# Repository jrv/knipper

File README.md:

# knipper
Simple 555 blinking leds schematic for car direction lights

This is a KiCad desing for the blinking lights of our Spijkstaal electric vehicle. It also switches the reverse lights via a MosFet, with a 5V signal from the motor controller.

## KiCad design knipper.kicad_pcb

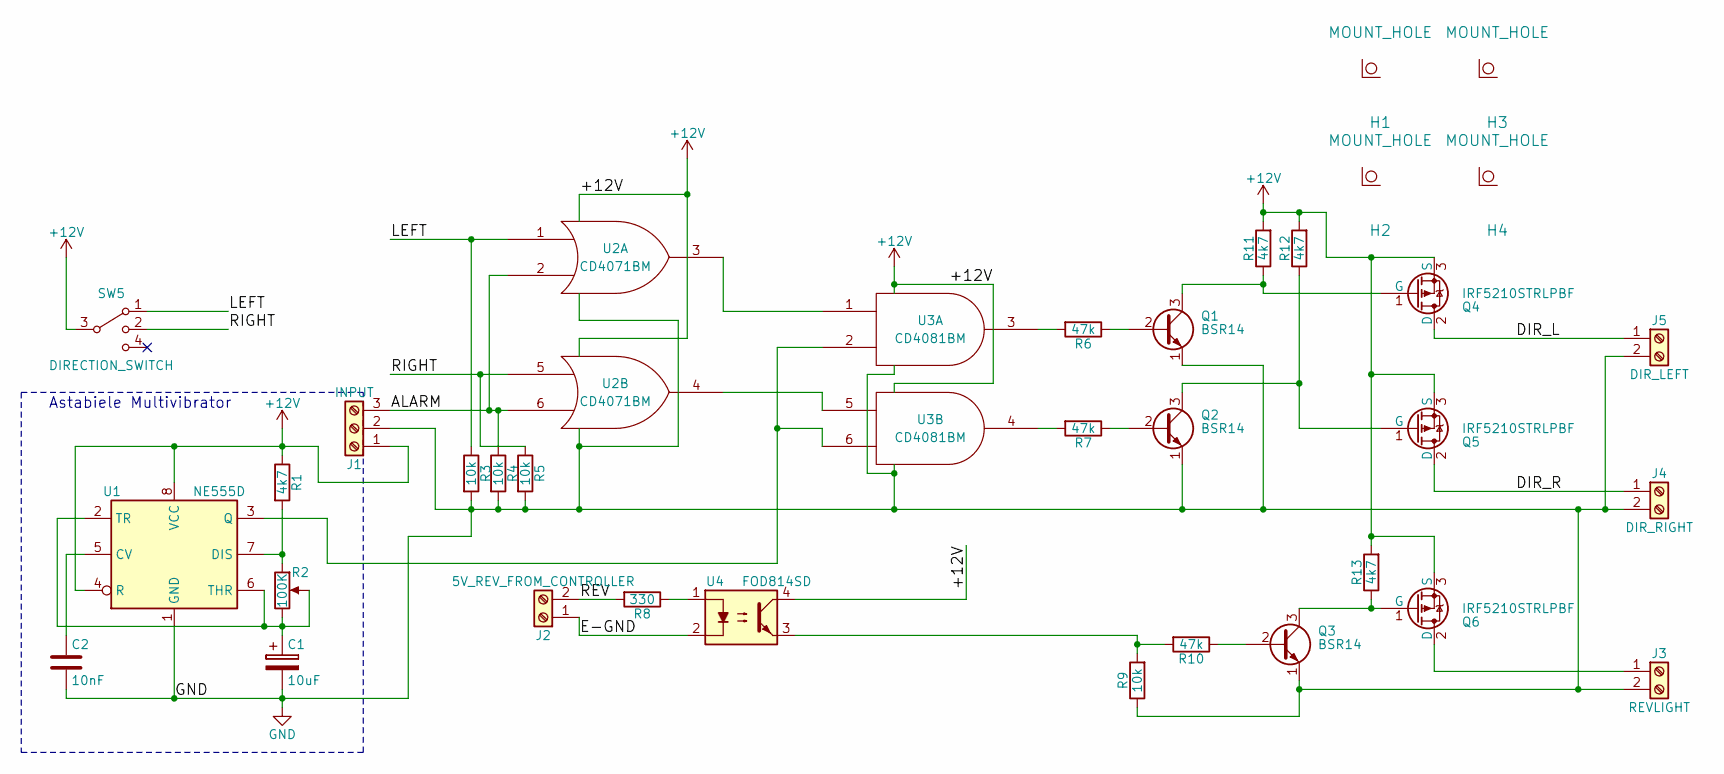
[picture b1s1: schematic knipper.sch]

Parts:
C1: 10uF; C_1206_HandSoldering; Farnell 1457413
C2: 10nF; C_0603_HandSoldering; Farnell 1414609
H1, H2, H3, H4: MOUNT_HOLE; MountingHole_3mm
J1: INPUT; AMP63824-3
J2: 5V_REV_FROM_CONTROLLER; PhoenixContact_MC-G_02x5.08mm_Angled
J3: REVLIGHT; AMP63824-2
J4: DIR_RIGHT; AMP63824-2
J5: DIR_LEFT; AMP63824-2
Q1, Q2, Q3: BSR14; SOT-23; Farnell 1700688
Q4, Q5, Q6: IRF5210STRLPBF; TO-263-3_TabPin2; Farnell 1298529
R1, R11, R12, R13: 4k7; R_0603_HandSoldering
R2: 100K; Potentiometer_Trimmer_Vishay_TS53YJ; Farnell 1141488
R3, R4, R5, R9: 10k; R_0603_HandSoldering
R6, R7, R10: 47k; R_0603_HandSoldering
R8: 330; R_0805_HandSoldering
SW5: DIRECTION_SWITCH; AMP63824-3
U1: NE555D; SOIC-8_3.9x4.9mm_Pitch1.27mm; Farnell 2782865
U2: CD4071BM; SOIC-14_N; Farnell 1739909
U3: CD4081BM; SOIC-14_N; Farnell 1122563
U4: FOD814SD; SMDIP-4_W9.53mm; Farnell 2453194

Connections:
+12V: J1.1, Q4.3 (S), Q5.3 (S), Q6.3 (S), R1.1, R11.2, R12.2, R13.2, SW5.3, U1.4 (R), U1.8 (VCC), U2.14 (VDD), U3.14 (VDD), U4.4
/ALARM: J1.3, R4.1, U2.2, U2.6
/DIR_L: J5.1, Q4.2 (D)
/DIR_R: J4.1, Q5.2 (D)
/E-GND: J2.1, U4.2
/LEFT: R3.1, SW5.1, U2.1
/REV: J2.2, R8.2
/RIGHT: R5.1, SW5.2, U2.5
GND: C1.2, C2.2, J1.2, J3.2, J4.2, J5.2, Q1.1 (E), Q2.1 (E), Q3.1 (E), R3.2, R4.2, R5.2, R9.1, U1.1 (GND), U2.7 (VSS), U3.7 (VSS)
unnamed: C1.1, R2.2, R2.3, U1.2 (TR), U1.6 (THR)
unnamed: C2.1, U1.5 (CV)
unnamed: J3.1, Q6.2 (D)
unnamed: Q1.2 (B), R6.1
unnamed: Q1.3 (C), Q4.1 (G), R11.1
unnamed: Q2.2 (B), R7.1
unnamed: Q2.3 (C), Q5.1 (G), R12.1
unnamed: Q3.2 (B), R10.1
unnamed: Q3.3 (C), Q6.1 (G), R13.1
unnamed: R1.2, R2.1, U1.7 (DIS)
unnamed: R6.2, U3.3
unnamed: R7.2, U3.4
unnamed: R8.1, U4.1
unnamed: R9.2, R10.2, U4.3
unnamed: U1.3 (Q), U3.2, U3.6
unnamed: U2.3, U3.1
unnamed: U2.4, U3.5

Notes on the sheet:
Astabiele Multivibrator

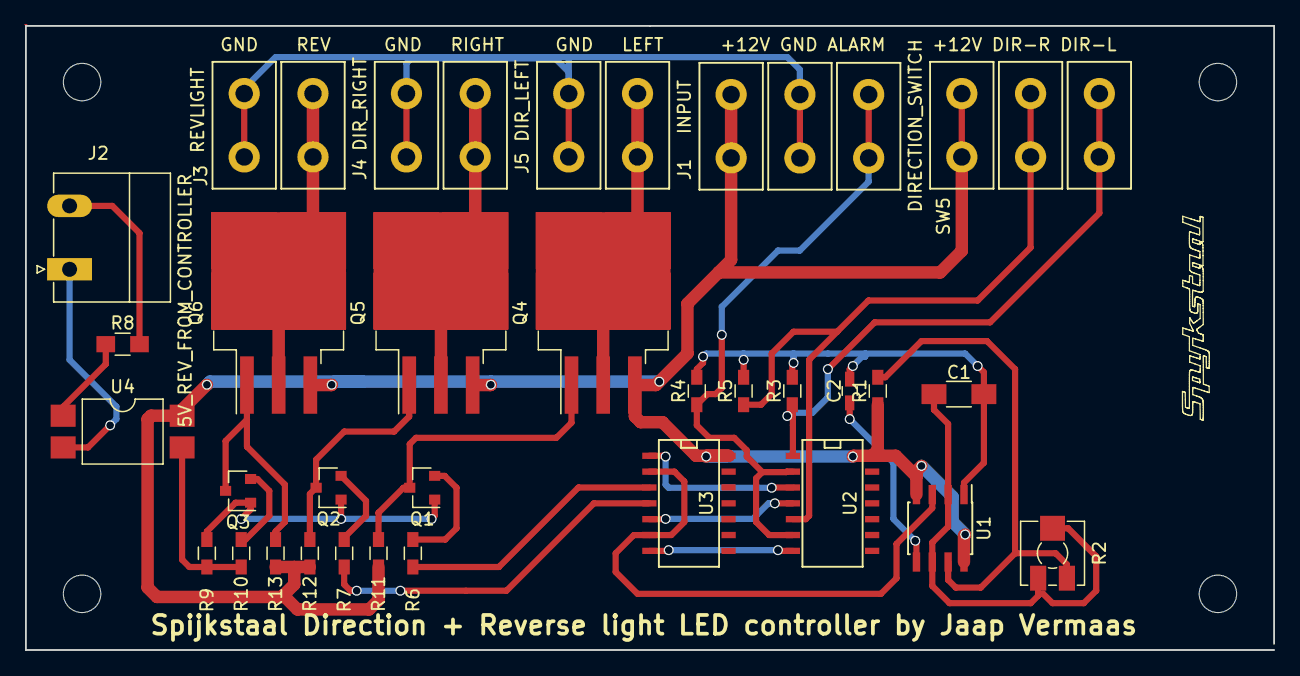
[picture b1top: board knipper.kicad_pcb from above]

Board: 2 copper layers, 100.0 x 50.0 mm, 35 parts (0 on the bottom side), 26 nets.

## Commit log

2017-10-16 re-ran KiCad to make sure no footprints were missing
2017-10-16 Bodemplaat tbv montage
2017-10-27 implemented high side switching
2017-10-28 gerbers for rel0.2
2017-10-28 Changed parts and layout to SMD
2017-11-22 created new gerbers for elecrow
